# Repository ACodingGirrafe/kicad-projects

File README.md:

# kicad-projects

My KiCad PCB projects. Each one lives in its own folder under `projects/` and is self-contained:
its custom symbols, footprints and 3D models sit in that project's `lib/` folder, so cloning
the repo and opening the `.kicad_pro` just works.

## Projects

| Project | Status | Description |
|---|---|---|
| [swing-pod](projects/swing-pod/) | v1.0, fab files ready | Badminton swing-tracker pod: XIAO ESP32-S3 + LSM6DSV16X IMU, 36 × 28 mm |
| [js-drone](projects/js-drone/) | Schematic | Flight controller schematic and PCB for an ESP32-based drone |
| [atfd](projects/atfd/) | Not started | A Tamagotchi for Daniela |

## Layout

```
projects/<name>/
├── <name>.kicad_pro / .kicad_sch / .kicad_pcb
├── sym-lib-table, fp-lib-table   # project libraries, paths relative to ${KIPRJMOD}
├── lib/                          # custom symbols (.kicad_sym), footprints (.pretty/), 3D models
├── outputs/                      # Gerbers, BOM, pick-and-place, schematic PDF, reports, renders
├── tools/                        # helper scripts, if any
└── README.md
```

## Starting a new project

1. Make `projects/<new-name>/` and create the KiCad project inside it.
2. Put any custom symbols/footprints in `projects/<new-name>/lib/` and add them under
   **Preferences → Manage Symbol/Footprint Libraries → Project Specific Libraries**
   with a path starting `${KIPRJMOD}/lib/...` (never an absolute `C:\Users\...` path).
3. Add a row to the table above.

## Versions

Use git tags (e.g. `swing-pod-v1.0`) for each board revision you send to fab,
rather than separate branches. Branches are for trying out changes you may throw away.

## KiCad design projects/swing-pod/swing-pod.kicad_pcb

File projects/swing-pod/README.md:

# swing-pod v1.0

An attempt to make PCB for a badminton swing-tracker pod for Jesus. A Seeed XIAO ESP32-S3 and a SparkFun Micro 6DoF IMU (LSM6DSV16X) sit on a 36 x 28 mm, 2-layer, 0.8 mm board. It charges through USB-C or through magnetic pogo pads. Made in KiCad 10.0.7.

## Files

| Path | What |
|---|---|
| `swing-pod.kicad_pro / .kicad_sch / .kicad_pcb` | KiCad project |
| `outputs/swing-pod-schematic.pdf` | Schematic |
| `outputs/swing-pod-gerbers-jlcpcb.zip` | Gerbers + Excellon drill (PTH/NPTH), upload to JLCPCB as-is |
| `outputs/gerbers/` | Same files unzipped, plus drill maps |
| `outputs/swing-pod-bom.csv` | BOM with manufacturer + MPN |
| `outputs/swing-pod-pos.csv` | Pick-and-place, mm, absolute coordinates (board top-left = 100,100) |
| `outputs/swing-pod-assembly.pdf` | Top assembly drawing (fab layer, all refdes) |
| `outputs/swing-pod-assembled.step` | Assembled 3D model for the housing fit check |
| `outputs/renders/` | Top, bottom, 3D renders and outline SVG |
| `outputs/erc-report.rpt`, `drc-report.rpt` | Final check reports |
| `lib/` | Project libraries (Seeed XIAO library, custom footprints, 3D models) |
| `tools/` | Scripts for the steps the KiCad MCP server can't do (see below) |

## Coordinate convention

- **+Y** is the board's top edge as drawn in KiCad, the edge with the USB-C connector. KiCad's own Y numbers get smaller toward it.
- **+X** is to the right, looking at the top side.
- The bottom silkscreen has a "+Y ^ USB-C" arrow.
- The USB-C shell overhangs the +Y edge by about 0.5 mm, so it reaches toward the housing wall opening.
- The board outline runs from (100,100) to (136,128) with 1 mm corner radii.

## Measured stack-up height (from the STEP models)

| From bottom of PCB to top of | Height |
|---|---|
| JST PH side-entry J1 (tallest part) | **5.65 mm** |
| SparkFun module (1.6 mm PCB + Qwiic connector) | 5.36 mm |
| XIAO USB-C shell | 5.26 mm |
| XIAO shield | 4.05 mm |
| U.FL + mated plug (Hirose spec, 2.5 mm max mated) | about 4.6 mm |

**5.65 mm is under the 6.0 mm budget.** That assumes the through-hole leads (J1, D1, wire pads) are trimmed flush on the bottom. Untrimmed, the JST pins stick out 2.6 mm below the board.

## Design rules (JLCPCB, conservative)

- 0.2 mm track and clearance, 0.6/0.3 mm vias, 0.3 mm copper-to-edge.
- `Power` netclass (VBAT, VUSB, POGO_P, GND): 0.5 mm tracks, 0.8/0.4 mm vias.
- GND pour on both layers.
- Keep-outs:
  - `ANTENNA_KEEPOUT` (both layers, no copper): x 117.2–127, y 118–128. That is the XIAO's U.FL corner and the strip below it.
  - `IMU_UNDERSIDE` (top layer only, no copper): under the flat-mounted SparkFun module's body.
- Mounting: **H1** (M2, bottom-right corner) plus the **SparkFun module's own M2 hole** (2.2 mm NPTH in footprint U2), which also clamps the module.

## Check results

- **ERC:** 0 violations.
- **DRC:** 0 errors, 0 unconnected items, 0 schematic-parity issues. 22 waived warnings, all from Seeed's XIAO footprint artwork:
  - 18 × silk over copper: the module outline is drawn across its own castellated pads. JLCPCB clips silkscreen off pads automatically.
  - 4 × silk past board edge: the outline around the USB-C overhang.
- **Netlist vs. spec** (`tools/check_netlist.py`, plus a separate check of the PCB pad nets): all 9 nets PASS.

| Spec line | Net | Pins |
|---|---|---|
| Battery + to XIAO BAT+ | VBAT | U1.23 (BAT+ pad), J1.1, J2.1, R1.1, TP5 |
| Battery − to XIAO BAT− | GND | U1.24 (BAT− pad), U1.13, U1.18, J1.2, J2.2, J3.2, U2.2, U2.6, R2.2, C1.2, TP2 |
| Pogo + to Schottky anode | POGO_P | J3.1 to D1.2 (A) |
| Schottky cathode to XIAO 5V | VUSB | D1.1 (K) to U1.14 (5V/VBUS), TP6 |
| Divider node to D2, 100 nF to GND | VBAT_SENSE | R1.2, R2.1, C1.1, U1.3 (D2/GPIO3), TP7 |
| IMU 3V3 and pull-ups to XIAO 3V3 | +3V3 | U1.12 (3V3), U2.1, R3.1, R4.1, TP1 |
| SDA | I2C_SDA | U2.3 to U1.5 (D4/GPIO5), R3.2, TP3 |
| SCL | I2C_SCL | U2.4 to U1.6 (D5/GPIO6), R4.2, TP4 |
| INT1 (deep-sleep wake) | IMU_INT1 | U2.5 to U1.2 (D1/GPIO2) |

XIAO pins used: D1 (GPIO2), D2 (GPIO3), D4 (GPIO5), D5 (GPIO6), 3V3, 5V, GND, plus the BAT+ and BAT− underside pads. Every other pin is marked no-connect. The GPIO mapping is checked against Seeed's wiki pin table.

## Verify by hand before you order or assemble

1. **Battery polarity.** J1 pin 1 (marked "+" on the silkscreen, rounded-rect pad) and J2's square pad are BAT+. JST-PH battery plugs come wired both ways. Measure your battery's plug with a meter and compare it to the board before you plug it in. Reversed polarity will destroy the XIAO's charger.
2. **XIAO BAT pads are underneath.** The XIAO is soldered flat by its castellations. Its BAT+ and BAT− pads face down onto this board, so an iron can't reach them. Each mating pad here has a 0.5 mm plated hole that is open on the bottom: feed solder through from below, or reflow or hot-plate the XIAO. Check continuity from J2 to the XIAO BAT pads afterwards.
3. **IMU module mounting.** The SparkFun board sits flat on footprint U2:
   - Its four underside test pads (GND, 3V3, SDA, SCL) land on pads that extend 1 mm past the module edge, so you can drag-solder them with an iron.
   - INT1 and GND use the module's two through-holes. Push a short wire or pin through both boards and solder both sides.
   - **The INT1 hole** is the one nearer the module's left long edge (looking at the board top, test pads toward you), about 5 mm from the far end. The GND hole is the matching one on the right. Confirm against the silkscreen on your module before soldering.
4. **SparkFun module jumpers:**
   - It already has 2.2 kΩ I2C pull-ups (jumper `I2C_PU`). Your 4.7 kΩ R3/R4 in parallel give about 1.5 kΩ, which works fine. Either cut `I2C_PU` or leave R3/R4 unfitted.
   - Cut the `LED` jumper to save about 0.7 mA in sleep.
   - Default I2C address is 0x6B.
5. **Diode, fit ONE of two:**
   - 1N5819 in DO-41, laid flat in the through-holes, **or**
   - a SOD-123 1 A Schottky on the centre pads, such as **B5819W**. SS14 is in SMA (DO-214AC) and does **not** fit SOD-123 pads.
   - The band (cathode) goes to the square pad, on the left.
6. **Battery plug clearance.** J1 is side-entry with its mouth facing −Y, toward the middle of the board. The mated plug and its wires lie over the J2/R1 area. Check in the STEP model that the wires have a path down to the battery.
7. **Antenna.** Route the U.FL cable and FPC antenna away from the battery and pogo wires. No copper is under the keep-out area.

## Footprints and models I made (not from a vendor library)

- `swing-pod:SparkFun_Micro_6DoF_LSM6DSV16X_Flat`: built from SparkFun's Eagle board file (19.05 × 7.62 mm, test pads at 1.905 mm pitch, 0.7 mm holes enlarged to 0.8 mm).
- `swing-pod:D_DO-41_P10.16mm_Horizontal_SOD-123_Alt`: KiCad's DO-41 and SOD-123 land patterns merged into one footprint.
- `swing-pod:WirePads_1x02_P3.0mm_D0.7mm`: two plated wire pads for 26–30 AWG wire.
- `lib/3d/SparkFun_Micro_6DoF.step`: a simple box model, not SparkFun's.
- `lib/3d/XIAO-ESP32S3.step`: Seeed's official model, re-oriented to fit the footprint.
- The XIAO symbol and footprint (`XIAO-ESP32-S3-SMD`) are **Seeed's official** files from their OPL KiCad library. They're unchanged except for the attached 3D model.

## Assumptions and open questions

- The board grew from about 34 × 26 to **36 × 28 mm** (your decision) to fit the side-entry JST. That leaves about 0.6 mm per side in the 37.2 × 29.3 bay, so check your print tolerance.
- The housing bay is assumed rectangular. Two M2 holes are provided: H1 at (133.6, 125.0) and the module hole at (104.6, 103.3).
- 1N5819 forward drop is about 0.3–0.45 V, so the XIAO charger sees about 4.6 V from a 5 V dock. That's fine for a single-cell LiPo.
- The divider draws about 4.5 µA from the battery at all times (470k + 470k).
- The BOM doesn't list LCSC numbers. Use JLCPCB's BOM matcher on the MPN column.
- The XIAO and the SparkFun module are hand-soldered modules, so leave them out of JLCPCB assembly if you order SMT assembly.

## Regenerating

`tools/` holds the steps the KiCad MCP server couldn't do. Run them with KiCad's Python (or a venv built with `--system-site-packages` on top of it):

- `board_extras.py`: keep-outs, and the BAT-pad vias open on the bottom.
- `sync_fields.py`: copies symbol fields, BOM flags and unconnected-net names to the PCB (the MCP sync skips them).
- `make_3d_models.py`: builds the XIAO and SparkFun 3D models. Needs `pip install cadquery-ocp`.
- `check_netlist.py`: compares the exported netlist against the connection spec. Run with any Python 3.

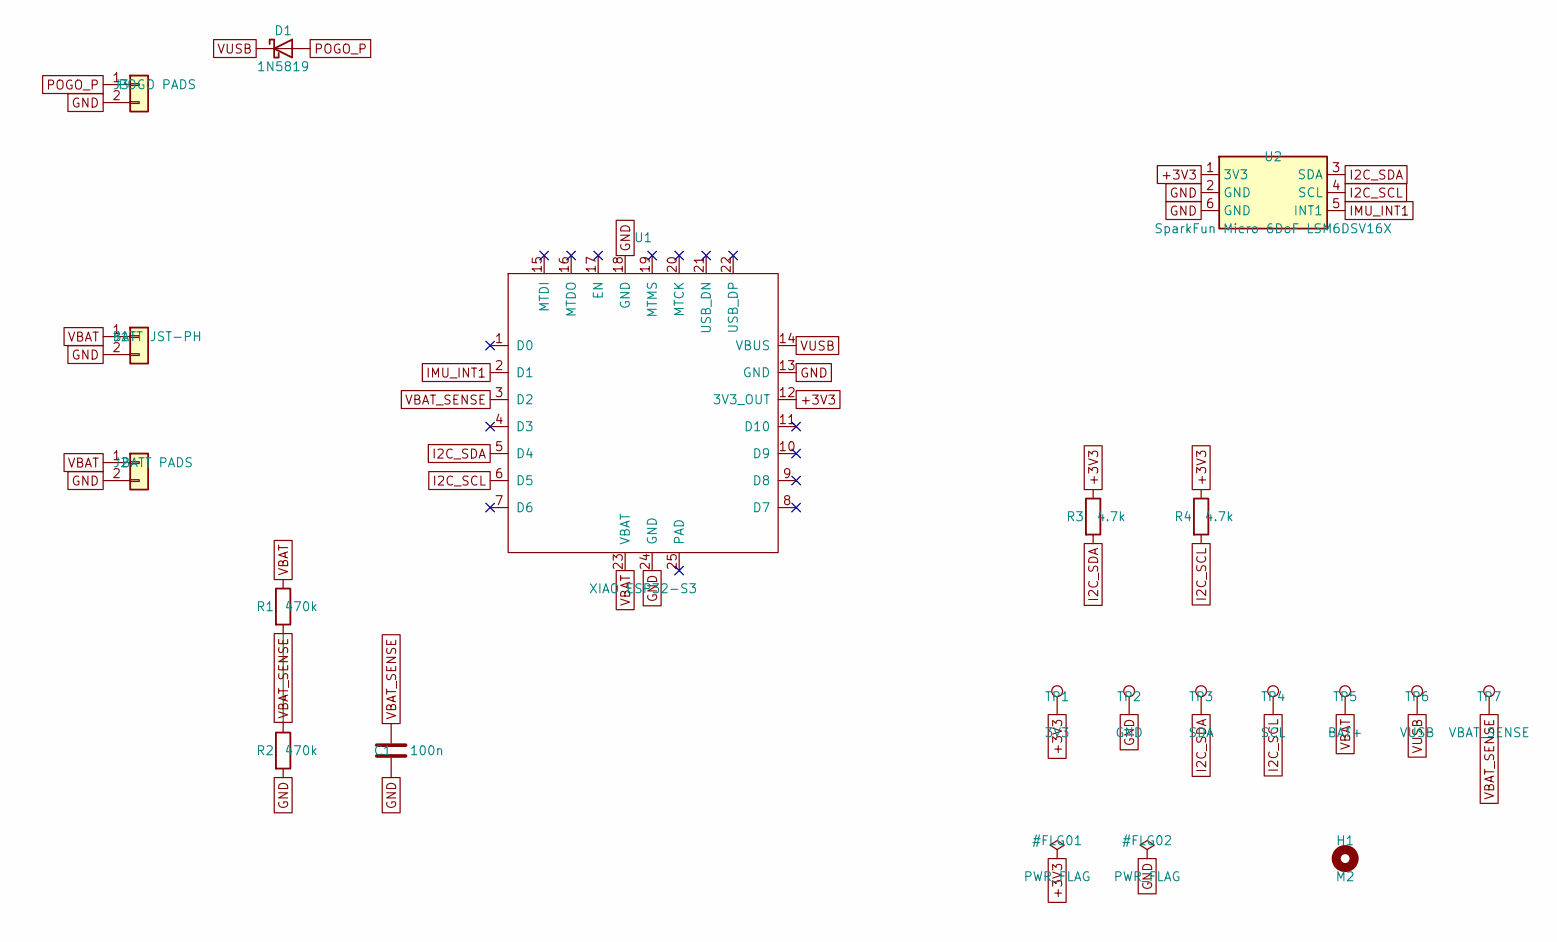
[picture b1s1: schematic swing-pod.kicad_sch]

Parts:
C1: 100n; C_0603_1608Metric; MPN CL10B104KB8NNNC
D1: 1N5819; D_DO-41_P10.16mm_Horizontal_SOD-123_Alt; MPN 1N5819-T
H1: M2; MountingHole_2.2mm_M2
J1: BATT JST-PH; JST_PH_S2B-PH-K_1x02_P2.00mm_Horizontal; MPN S2B-PH-K-S(LF)(SN)
J2: BATT PADS; WirePads_1x02_P3.0mm_D0.7mm
J3: POGO PADS; WirePads_1x02_P3.0mm_D0.7mm
R1, R2: 470k; R_0603_1608Metric; MPN RC0603FR-07470KL
R3, R4: 4.7k; R_0603_1608Metric; MPN RC0603FR-074K7L
TP1: 3V3; TestPoint_Pad_D1.0mm
TP2: GND; TestPoint_Pad_D1.0mm
TP3: SDA; TestPoint_Pad_D1.0mm
TP4: SCL; TestPoint_Pad_D1.0mm
TP5: BAT+; TestPoint_Pad_D1.0mm
TP6: VUSB; TestPoint_Pad_D1.0mm
TP7: VBAT_SENSE; TestPoint_Pad_D1.0mm
U1: XIAO ESP32-S3; XIAO-ESP32-S3-SMD; MPN 113991114
U2: SparkFun Micro 6DoF LSM6DSV16X; SparkFun_Micro_6DoF_LSM6DSV16X_Flat; MPN SEN-21336

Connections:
+3V3: R3.1, R4.1, TP1.1, U1.12 (3V3_OUT), U2.1 (3V3)
GND: C1.2, J1.2, J2.2, J3.2, R2.2, TP2.1, U1.13 (GND), U1.18 (GND), U1.24 (GND), U2.2 (GND), U2.6 (GND)
I2C_SCL: R4.2, TP4.1, U1.6 (D5), U2.4 (SCL)
I2C_SDA: R3.2, TP3.1, U1.5 (D4), U2.3 (SDA)
IMU_INT1: U1.2 (D1), U2.5 (INT1)
POGO_P: D1.2 (A), J3.1
VBAT: J1.1, J2.1, R1.1, TP5.1, U1.23 (VBAT)
VBAT_SENSE: C1.1, R1.2, R2.1, TP7.1, U1.3 (D2)
VUSB: D1.1 (K), TP6.1, U1.14 (VBUS)

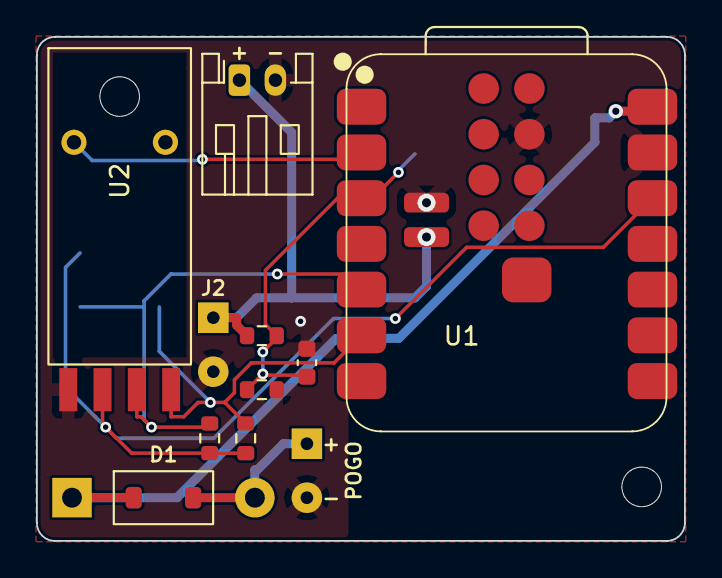
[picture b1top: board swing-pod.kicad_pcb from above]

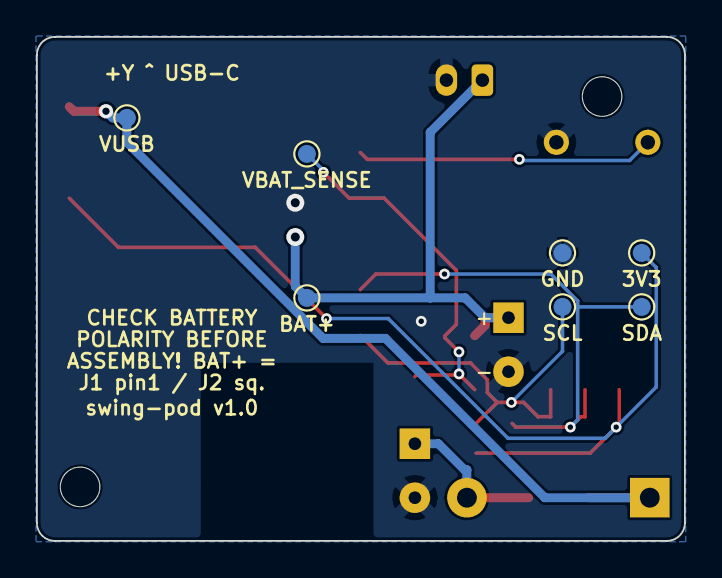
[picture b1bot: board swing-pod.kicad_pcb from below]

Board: 2 copper layers, 36.0 x 28.0 mm, 19 parts (7 on the bottom side), 9 nets.

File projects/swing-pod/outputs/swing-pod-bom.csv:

"Designator","Value","Footprint","Qty","Manufacturer","MPN","Alternate","DNP"
"C1","100n","Capacitor_SMD:C_0603_1608Metric","1","Samsung","CL10B104KB8NNNC","",""
"D1","1N5819","swing-pod:D_DO-41_P10.16mm_Horizontal_SOD-123_Alt","1","Diodes Inc.","1N5819-T","B5819W (SOD-123; SS14 is SMA and does NOT fit)",""
"J1","BATT JST-PH","Connector_JST:JST_PH_S2B-PH-K_1x02_P2.00mm_Horizontal","1","JST","S2B-PH-K-S(LF)(SN)","",""
"R1,R2","470k","Resistor_SMD:R_0603_1608Metric","2","Yageo","RC0603FR-07470KL","",""
"R3,R4","4.7k","Resistor_SMD:R_0603_1608Metric","2","Yageo","RC0603FR-074K7L","",""
"U1","XIAO ESP32-S3","Seeed_Studio_XIAO_Series:XIAO-ESP32-S3-SMD","1","Seeed Studio","113991114","",""
"U2","SparkFun Micro 6DoF LSM6DSV16X","swing-pod:SparkFun_Micro_6DoF_LSM6DSV16X_Flat","1","SparkFun","SEN-21336","",""
